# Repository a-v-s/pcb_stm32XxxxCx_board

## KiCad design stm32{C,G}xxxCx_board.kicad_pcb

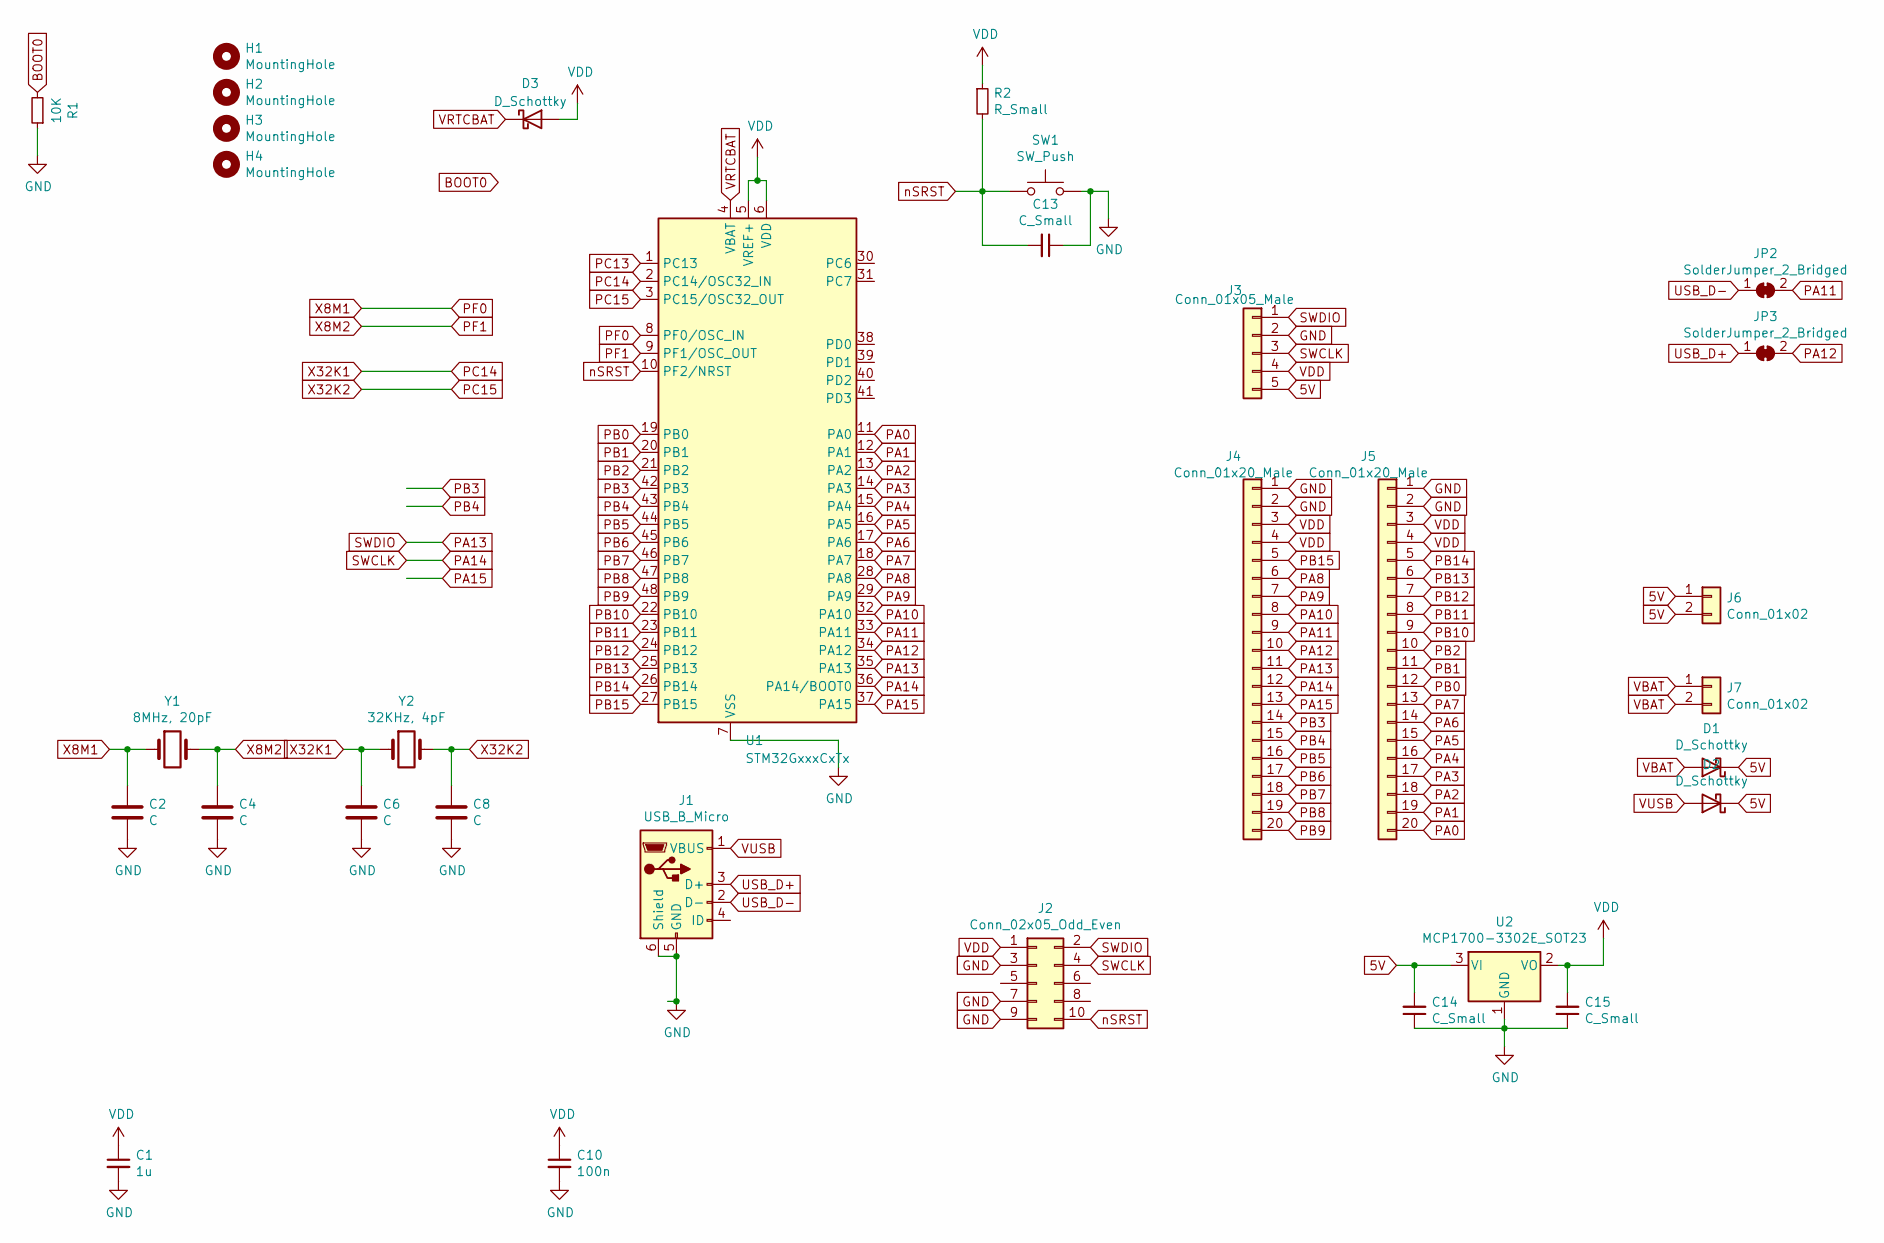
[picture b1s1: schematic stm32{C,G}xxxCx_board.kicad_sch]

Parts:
C1: 1u; C_0805_2012Metric
C2, C4, C6, C8: C; C_0805_2012Metric
C10: 100n; C_0805_2012Metric
C13, C14, C15: C_Small; C_0805_2012Metric
D1, D2, D3: D_Schottky; D_0805_2012Metric
H1, H2, H3, H4: MountingHole; MountingHole_2.2mm_M2_ISO7380
J1: USB_B_Micro; USB_Micro-B_Wuerth_629105150521
J2: Conn_02x05_Odd_Even; PinHeader_2x05_P1.27mm_Vertical
J3: Conn_01x05_Male; PinHeader_1x05_P2.54mm_Vertical
J4, J5: Conn_01x20_Male; PinHeader_1x20_P2.54mm_Vertical
J6, J7: Conn_01x02; PinHeader_1x02_P2.54mm_Vertical
JP2, JP3: SolderJumper_2_Bridged; SolderJumper-2_P1.3mm_Bridged_RoundedPad1.0x1.5mm
R1: 10K; R_0805_2012Metric
R2: R_Small; R_0805_2012Metric
SW1: SW_Push; TS-1187
U1: STM32GxxxCxTx; LQFP-48_7x7mm_P0.5mm
U2: MCP1700-3302E_SOT23; SOT-23
Y1: 8MHz, 20pF; Crystal_SMD_5032-2Pin_5.0x3.2mm
Y2: 32KHz, 4pF; Crystal_SMD_EuroQuartz_EQ161-2Pin_3.2x1.5mm

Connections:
5V: C14.2, D1.1 (K), D2.1 (K), J3.5, J6.1, J6.2, U2.3 (VI)
BOOT0: R1.2
GND: C1.2, C2.2, C4.2, C6.2, C8.2, C10.2, C13.1, C14.1, C15.1, J1.5 (GND), J1.6 (Shield), J2.3, J2.7, J2.9, J3.2, J4.1, J4.2, J5.1, J5.2, R1.1, SW1.2, U1.7 (VSS), U2.1 (GND)
PA0: J5.20, U1.11 (PA0)
PA1: J5.19, U1.12 (PA1)
PA2: J5.18, U1.13 (PA2)
PA3: J5.17, U1.14 (PA3)
PA4: J5.16, U1.15 (PA4)
PA5: J5.15, U1.16 (PA5)
PA6: J5.14, U1.17 (PA6)
PA7: J5.13, U1.18 (PA7)
PA8: J4.6, U1.28 (PA8)
PA9: J4.7, U1.29 (PA9)
PA10: J4.8, U1.32 (PA10)
PA11: J4.9, JP2.2 (B), U1.33 (PA11)
PA12: J4.10, JP3.2 (B), U1.34 (PA12)
PA13: J2.2, J3.1, J4.11, U1.35 (PA13)
PA14: J2.4, J3.3, J4.12, U1.36 (PA14/BOOT0)
PA15: J4.13, U1.37 (PA15)
PB0: J5.12, U1.19 (PB0)
PB1: J5.11, U1.20 (PB1)
PB2: J5.10, U1.21 (PB2)
PB3: J4.14, U1.42 (PB3)
PB4: J4.15, U1.43 (PB4)
PB5: J4.16, U1.44 (PB5)
PB6: J4.17, U1.45 (PB6)
PB7: J4.18, U1.46 (PB7)
PB8: J4.19, U1.47 (PB8)
PB9: J4.20, U1.48 (PB9)
PB10: J5.9, U1.22 (PB10)
PB11: J5.8, U1.23 (PB11)
PB12: J5.7, U1.24 (PB12)
PB13: J5.6, U1.25 (PB13)
PB14: J5.5, U1.26 (PB14)
PB15: J4.5, U1.27 (PB15)
PC13: U1.1 (PC13)
PC14: C6.1, U1.2 (PC14/OSC32_IN), Y2.1
PC15: C8.1, U1.3 (PC15/OSC32_OUT), Y2.2
PF0: C2.1, U1.8 (PF0/OSC_IN), Y1.1
PF1: C4.1, U1.9 (PF1/OSC_OUT), Y1.2
USB_D+: J1.3 (D+), JP3.1 (A)
USB_D-: J1.2 (D-), JP2.1 (A)
VBAT: D1.2 (A), J7.1, J7.2
VDD: C1.1, C10.1, C15.2, D3.2 (A), J2.1, J3.4, J4.3, J4.4, J5.3, J5.4, R2.1, U1.5 (VREF+), U1.6 (VDD), U2.2 (VO)
VRTCBAT: D3.1 (K), U1.4 (VBAT)
VUSB: D2.2 (A), J1.1 (VBUS)
nSRST: C13.2, J2.10, R2.2, SW1.1, U1.10 (PF2/NRST)

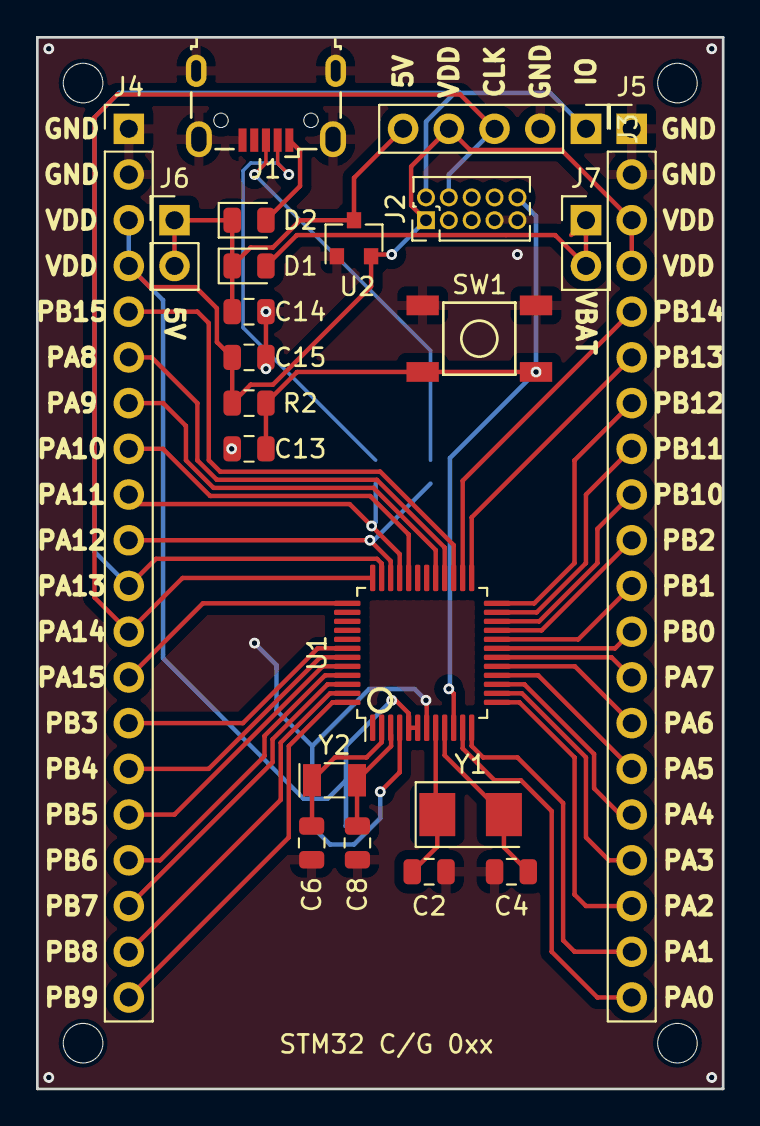
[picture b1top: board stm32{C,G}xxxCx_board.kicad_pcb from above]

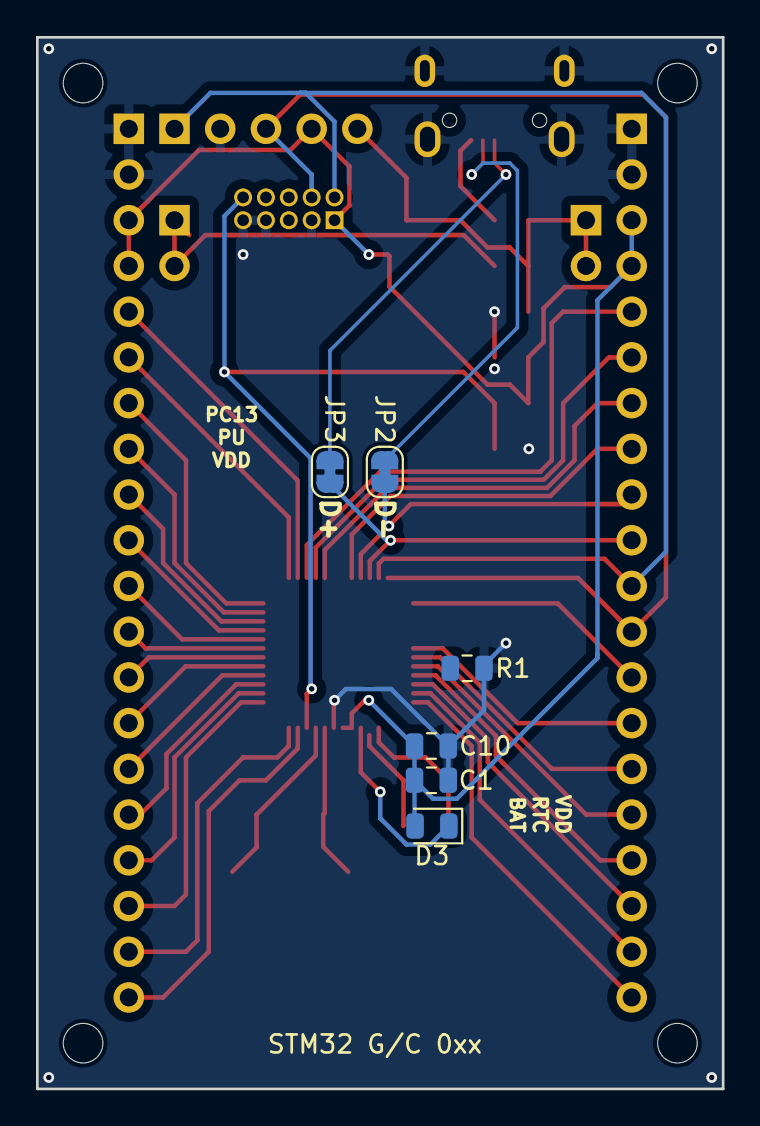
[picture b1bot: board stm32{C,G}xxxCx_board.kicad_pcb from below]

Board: 2 copper layers, 38.1 x 58.4 mm, 32 parts (6 on the bottom side), 45 nets.

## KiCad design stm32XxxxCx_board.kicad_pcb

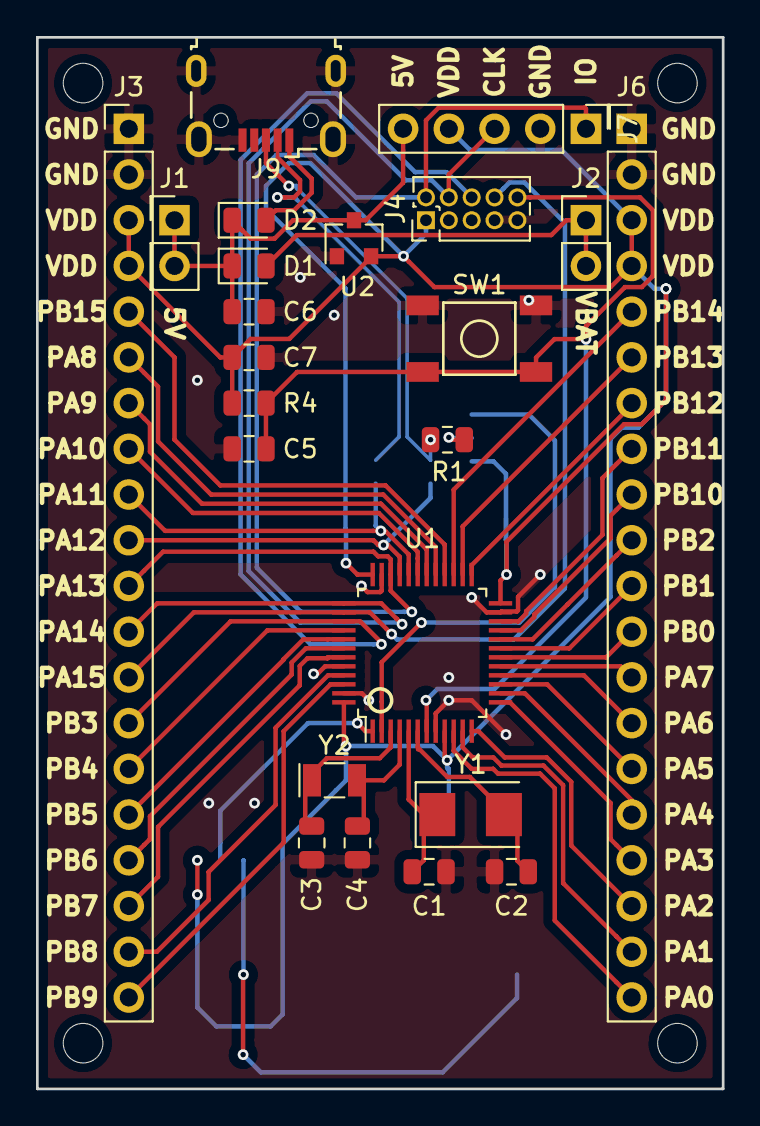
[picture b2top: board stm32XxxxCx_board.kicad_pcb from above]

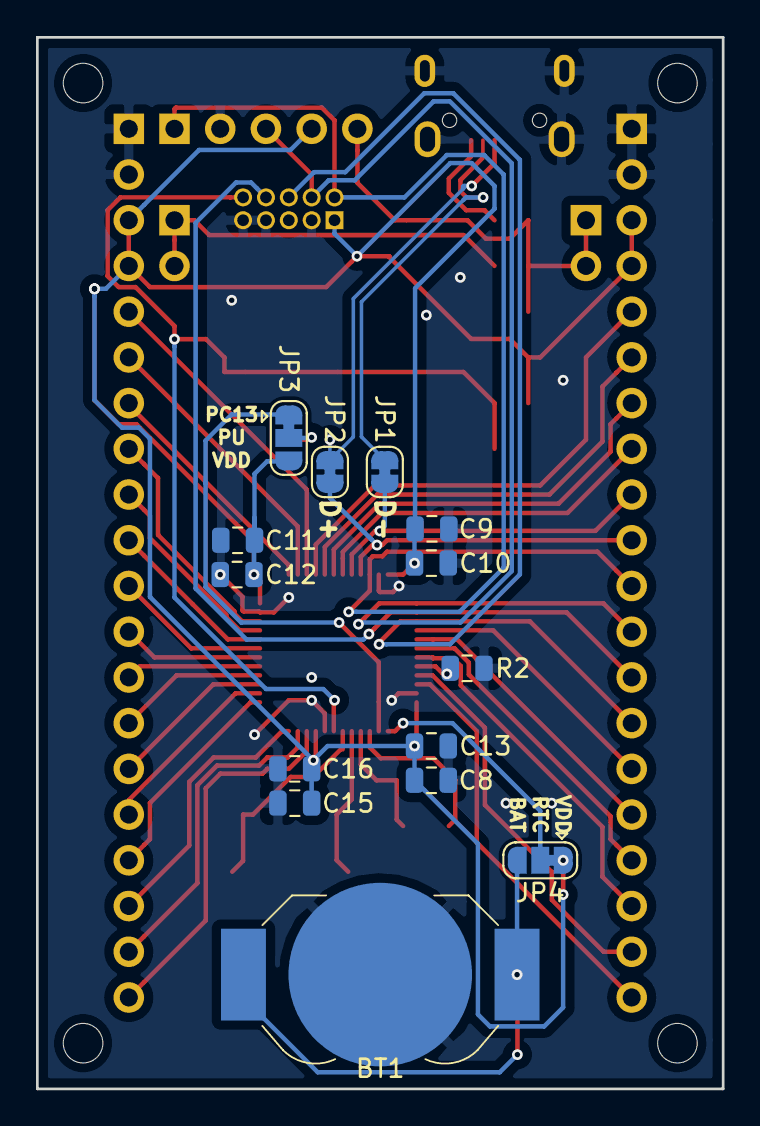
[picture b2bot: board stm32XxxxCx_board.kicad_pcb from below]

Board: 2 copper layers, 38.1 x 58.4 mm, 41 parts (14 on the bottom side), 49 nets.

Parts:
BT1: Battery_Cell; BatteryHolder_LINX_BAT-HLD-012-SMT
C1, C2, C3, C4: C; C_0805_2012Metric
C5, C6, C7: C_Small; C_0805_2012Metric
C8, C10, C12, C15: 1u; C_0805_2012Metric
C9, C11, C13, C16: 100n; C_0805_2012Metric
D1, D2: D_Schottky; D_0805_2012Metric
H1, H2, H3, H4: MountingHole; MountingHole_2.2mm_M2_ISO7380
J1, J2: Conn_01x02; PinHeader_1x02_P2.54mm_Vertical
J3, J6: Conn_01x20_Male; PinHeader_1x20_P2.54mm_Vertical
J4: Conn_02x05_Odd_Even; PinHeader_2x05_P1.27mm_Vertical
J7: Conn_01x05_Male; PinHeader_1x05_P2.54mm_Vertical
J9: USB_B_Micro; USB_Micro-B_Wuerth_629105150521
JP1, JP2: SolderJumper_2_Bridged; SolderJumper-2_P1.3mm_Bridged_RoundedPad1.0x1.5mm
JP3, JP4: SolderJumper_3_Bridged12; SolderJumper-3_P1.3mm_Bridged12_RoundedPad1.0x1.5mm
R1: 1K5; R_0805_2012Metric
R2: 10K; R_0805_2012Metric
R4: R_Small; R_0805_2012Metric
SW1: SW_Push; TS-1187
U1: STM32F103CBTx; LQFP-48_7x7mm_P0.5mm
U2: MCP1700-3302E_SOT23; SOT-23
Y1: 8MHz, 20pF; Crystal_SMD_5032-2Pin_5.0x3.2mm
Y2: 32KHz, 4pF; Crystal_SMD_EuroQuartz_EQ161-2Pin_3.2x1.5mm

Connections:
5V: C6.2, D1.1, D2.1, J1.1, J1.2, J7.5, U2.3
BOOT0: R2.2, U1.44
GND: BT1.2, C1.2, C2.2, C3.2, C4.2, C5.1, C6.1, C7.1, C8.2, C9.2, C10.2, C11.2, C12.2, C13.2, C15.2, C16.2, J3.1, J3.2, J4.3, J4.7, J4.9, J6.1, J6.2, J7.2, J9.5, J9.6, R2.1, SW1.2, U1.8, U1.23, U1.35, U1.47, U2.1
unnamed: BT1.1, JP4.3
unnamed: JP3.2, R1.1
PA0: J6.20, U1.10
PA1: J6.19, U1.11
PA2: J6.18, U1.12
PA3: J6.17, U1.13
PA4: J6.16, U1.14
PA5: J6.15, U1.15
PA6: J6.14, U1.16
PA7: J6.13, U1.17
PA8: J3.6, U1.29
PA9: J3.7, U1.30
PA10: J3.8, U1.31
PA11: J3.9, JP1.2, U1.32
PA12: J3.10, JP2.2, U1.33
PA13: J3.11, J4.2, J7.1, U1.34
PA14: J3.12, J4.4, J7.3, U1.37
PA15: J3.13, J4.8, U1.38
PB0: J6.12, U1.18
PB1: J6.11, U1.19
PB2: J6.10, U1.20
PB3: J3.14, J4.6, U1.39
PB4: J3.15, U1.40
PB5: J3.16, U1.41
PB6: J3.17, U1.42
PB7: J3.18, U1.43
PB8: J3.19, U1.45
PB9: J3.20, U1.46
PB10: J6.9, U1.21
PB11: J6.8, U1.22
PB12: J6.7, U1.25
PB13: J6.6, U1.26
PB14: J6.5, U1.27
PB15: J3.5, U1.28
PC13: JP3.1, U1.2
PC14: C3.1, U1.3, Y2.1
PC15: C4.1, U1.4, Y2.2
PF0: C1.1, U1.5, Y1.1
PF1: C2.1, U1.6, Y1.2
USB_D+: J9.3, JP2.1, R1.2
USB_D-: J9.2, JP1.1
VBAT: D1.2, J2.1, J2.2
VDD: C7.2, C8.1, C9.1, C10.1, C11.1, C12.1, C13.1, C15.1, C16.1, J3.3, J3.4, J4.1, J6.3, J6.4, J7.4, JP3.3, JP4.1, R4.1, U1.9, U1.24, U1.36, U1.48, U2.2
VRTCBAT: JP4.2, U1.1
VUSB: D2.2, J9.1
nSRST: C5.2, J4.10, R4.2, SW1.1, U1.7

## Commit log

2018-12-24 Initial commit - routed
2018-12-29 What changed here?
2018-12-29 Anotherattempt + more bypass caps
2018-12-29 Almost routed
2019-01-03 Routed - with bypass caps on the back
2019-02-04 Handsoldering->Normal, USB to ROUND
2019-11-03 Fix USB connector swapped D+/D- pins
2020-01-04 Board ver 3.1
2023-03-26 new boards
2023-03-26 silkscreen add text
